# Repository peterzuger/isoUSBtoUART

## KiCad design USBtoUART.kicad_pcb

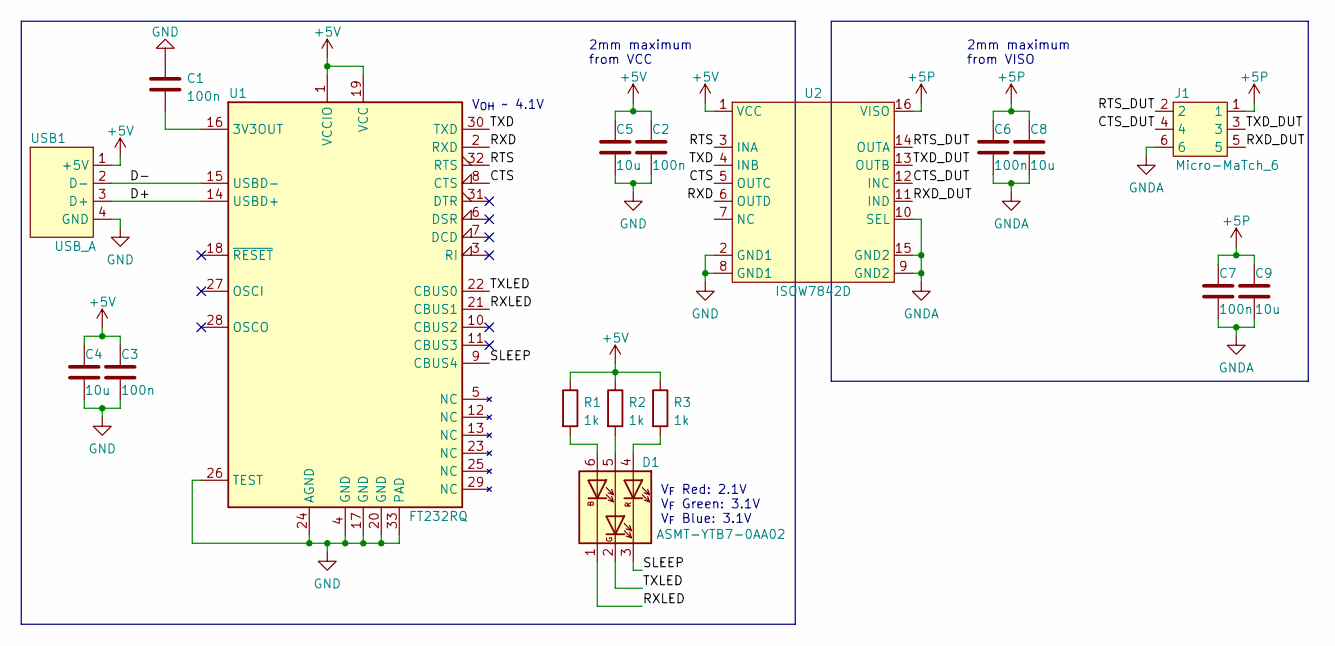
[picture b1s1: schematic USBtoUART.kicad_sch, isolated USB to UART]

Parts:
C1, C2, C3, C6, C7: 100n; C_0402_1005Metric
C4, C5, C8, C9: 10u; C_0402_1005Metric
D1: ASMT-YTB7-0AA02; LED_Avago_PLCC6_3x2.8mm
J1: Micro-MaTch_6
R1, R2, R3: 1k; R_0402_1005Metric
U1: FT232RQ; QFN-32-1EP_5x5mm_P0.5mm_EP3.3x3.3mm
U2: ISOW7842D; SOIC-16W_7.5x10.3mm_P1.27mm_HV
USB1: USB_A

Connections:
+5P: C6.1, C7.1, C8.1, C9.1, J1.1, U2.16 (VISO)
+5V: C2.1, C3.1, C4.1, C5.1, R1.1, R2.1, R3.1, U1.1 (VCCIO), U1.19 (VCC), U2.1 (VCC), USB1.1 (+5V); also elsewhere on the board
/CTS: U1.8 (CTS), U2.5 (OUTC)
/CTS_DUT: J1.4, U2.12 (INC)
/D+: U1.14 (USBD+), USB1.3 (D+)
/D-: U1.15 (USBD-), USB1.2 (D-)
/RTS: U1.32 (RTS), U2.3 (INA)
/RTS_DUT: J1.2, U2.14 (OUTA)
/RXD: U1.2 (RXD), U2.6 (OUTD)
/RXD_DUT: J1.5, U2.11 (IND)
/RXLED: D1.1 (KB), U1.21 (CBUS1)
/SLEEP: D1.3 (KR), U1.9 (CBUS4)
/TXD: U1.30 (TXD), U2.4 (INB)
/TXD_DUT: J1.3, U2.13 (OUTB)
/TXLED: D1.2 (KG), U1.22 (CBUS0)
GND: C1.1, C2.2, C3.2, C4.2, C5.2, U1.4 (GND), U1.17 (GND), U1.20 (GND), U1.24 (AGND), U1.26 (TEST), U1.33 (PAD), U2.2 (GND1), U2.8 (GND1), USB1.4 (GND)
GNDA: C6.2, C7.2, C8.2, C9.2, J1.6, U2.9 (GND2), U2.10 (SEL), U2.15 (GND2)
unnamed: C1.2, U1.16 (3V3OUT)
unnamed 18: D1.4 (AR), R3.2; also elsewhere on the board
unnamed: D1.5 (AG), R2.2
unnamed: D1.6 (AB), R1.2

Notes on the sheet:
2mm maximum from VCC
2mm maximum from VISO
V_{OH} ~ 4.1V
V_{F} Red: 2.1V V_{F} Green: 3.1V V_{F} Blue: 3.1V

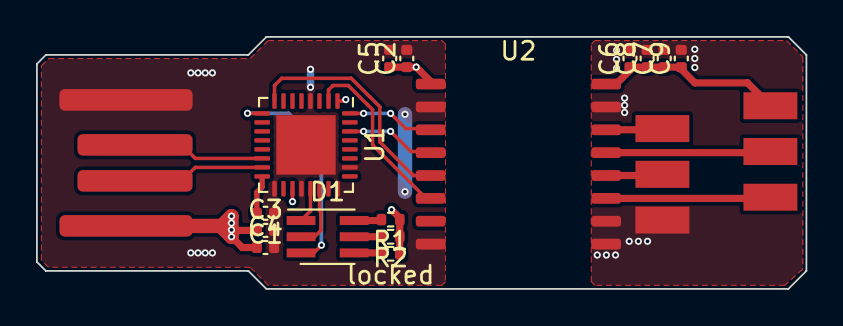
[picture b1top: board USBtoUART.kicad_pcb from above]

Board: 2 copper layers, 42.8 x 14.0 mm, 17 parts (0 on the bottom side), 21 nets.

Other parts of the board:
locked: 1k; R_0402_1005Metric

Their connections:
+5V: locked.1; also elsewhere on the board
unnamed 18: locked.2; also elsewhere on the board

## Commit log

2018-01-27 added LICENSE
2018-01-27 version 1.0
2018-01-27 version 2.0
2022-12-17 added PDF version of the schematic
2022-12-17 version 2.1 in KiCad
2022-12-17 added panel.json for panelizing the board using KiKit
    added a Makefile for ease of use.
    ignore the generated panel directory

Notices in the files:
USBtoUART.kicad_pcb:
© 2022
